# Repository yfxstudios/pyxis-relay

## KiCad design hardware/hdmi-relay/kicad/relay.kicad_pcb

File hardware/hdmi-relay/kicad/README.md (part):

# Carrier board rev A: KiCad project

**Current state (Oct 25):** schematic and board complete, ERC 0, DRC with schematic parity 0/0/0, fab outputs in
`fab/` (J301 hand-fitted, kept out of the JLCPCB BOM and CPL). The latest review is `REVIEW_FINAL_5.md`; the
sections below are the design history in date order, so the early ones describe drafts that no longer apply.

Open `relay.kicad_pro` in KiCad 10. **[relay.pdf](relay.pdf)** is the schematic as a PDF, 8 pages.

The schematic is **generated** from the Python files in `gen/`, one per sheet, so every connection is written down
next to the reason for it.

```bash
gen/check.sh        # regenerate, run KiCad's electrical rules check (ERC), print problems and every net
```

After editing a `gen/*.py` file, run it again; the `.kicad_sch` files are overwritten. If you'd rather edit in
KiCad's editor from here on, that's fine too: stop using the generator, since a regenerate would undo those edits.

## Sheets

| Sheet | File | What's on it |
|---|---|---|
| Power | `gen/power.py` | DC jack (PJ-002AH), NP-F contacts, USB-C with CH224A (PD 9 V), Schottky OR, fuse, TVS, battery sense, two SY8303 (5V_SOM for the module, 5V_SYS), two TPS563201 (3V3_IO, 1V1_628) |
| HDMI in (RK628D) | `gen/hdmi_in.py` | HDMI connector, ESD, plug detect, DDC, CEC and HPD; RK628D with its power switch, filtering and decoupling; 24 MHz crystal; CSI-2 x4 out. Copied from the DshanPi-A1 V1.1 schematic, pages 31–32. |
| HDMI out | `gen/board_io_sheets.py` | HDMI connector from the module's HDMI TX, ESD, 5 V current-limited switch (DDC/HPD level-shifted on the module) |
| Ethernet | `gen/ethernet.py` | Gigabit jack with magnetics and centre-tap capacitors; the PHY is on the Radxa CM3 |
| M.2 Wi-Fi + Bluetooth | `gen/board_io_sheets.py` | M.2 2230 E-key socket for the RTL8822CE: PCIe x1 for Wi-Fi, USB 2.0 for Bluetooth |
| Debug, buttons, LEDs, SDI | `gen/board_io_sheets.py` | Debug UART header, RESET and RECOVERY buttons, three LEDs, 2 × 20 SDI add-on header (not fitted), mounting holes |
| Module: Radxa CM3 | `gen/module.py`, `gen/cm3_pinout.json` | The three DF40 receptacles with Radxa's pin names (module revision V1.32+), every pin assigned or no-connect; recovery pull-up, VBUSDET, decoupling |

**Status (schematic draft 1, Oct 21; superseded, see the top):**
- ERC passed with one warning: the M.2 socket footprint wasn't made yet.
- 191 parts.
- Every RK628D ball (144) is assigned and checked against the datasheet ball map.
- Every Radxa CM3 pin (300) is assigned or marked unused; the build fails if one is missed or used twice.

## Before this could become a board (Oct 21 list, all done since)

1. **Check the module connectors:**
   - Compare our three DF40 receptacles with Radxa's IO-board connector data
     (`../datasheets/radxa_cm3_io_board_b2b_connector_20230718.asc`): pin 1 orientation, the spacing between
     connectors, and the M2.5 mounting holes.
   - J68's pads are Radxa pins 101–200 minus 100; check that against the IO board too.
2. **Footprints still to make or confirm:**
   - **M.2 E-key socket:** for the chosen part.
   - **Gigabit magjack:** pick an LCSC part with the Pulse JK0654219 pinout, or redo that footprint.
   - **HDMI connector:** the bought LCSC part (C2902698) vs. the Molex footprint used now.
   - **RK628D:** check the generated 0.65 mm BGA footprint (`relay.pretty/`) against the datasheet land pattern
     and JLCPCB's BGA rules.
   - **Locking DC jack:** pick it together with the case.
3. **Values to confirm:**
   - **Crystal load capacitors (18 pF):** match the chosen 24 MHz crystal's rated load capacitance.
   - **Inductor saturation currents.**
   - **The RK628D 1.1 V current:** for the Rockchip RK628D hardware design guide, which we don't have yet.
4. **Layout:** 4-layer impedance-controlled stack, rules in `../REV_A_SPEC.md` section 6, length limits from the
   Radxa CM3 datasheet.

## Board: first placement (Oct 22)

`relay.kicad_pcb` is generated by `gen/pcb.py` from the schematic netlist. Run it with KiCad's bundled Python:

```bash
/Applications/KiCad/KiCad.app/Contents/Frameworks/Python.framework/Versions/Current/bin/python3 gen/pcb.py
```

Renders: [3D view](renders/rev_a_placement_3d.png), [top view](renders/rev_a_placement_top.png).

**What it sets up:**
- **Board:** 120 × 100 mm, 4 layers.
- **Front panel:** HDMI IN and HDMI OUT.
- **Back panel:** USB-C, DC, the NP-F lead and RJ45.
- **Net classes:** in `relay.kicad_pro`.

  | Class | Width / gap |
  |---|---|
  | 100 Ω differential (HDMI, CSI, Ethernet) | 0.10 / 0.10 mm |
  | 90 Ω differential (USB) | 0.12 / 0.10 mm |
  | 85 Ω differential (PCIe) | 0.14 / 0.10 mm |
  | Power | 0.5 mm |
  | Default | 0.127 mm |

  These are first estimates for JLCPCB's JLC04161H-3313 stackup. **Confirm each with JLCPCB's impedance
  calculator.**
- **Module connectors and mounting holes:** copied from Radxa's own CM3 IO board (`relay.pretty/Radxa_CM3_*`,
  from `../datasheets/radxa_cm3_io_board_b2b_connector_20230718.asc`). The three receptacles and the four M2.5
  holes share one origin, so their spacing matches Radxa's working board exactly. Radxa's pad rows are 2.66 mm
  apart, against 3.08 mm in KiCad's stock DF40 footprint, so ours copy Radxa's.

**Placement:**
- **The CM3** sits in the middle, turned so J68 (camera input, HDMI out, PCIe) faces the front.
- **The RK628D** is between HDMI IN and the CM3's camera pins, so that run is short.
- **The M.2 Wi-Fi socket** is on the left, with the card lying over the board.
- **Power** is along the back-left; the SDI header (not fitted) is on the right.
- **Small parts** are packed by sheet into regions near their main chip (`REGIONS` in `gen/pcb.py`).

**DRC:** no clearance, short or overlap errors. What remains:
- **499 unrouted connections:** routing is next.
- **Labels overlapping:** cosmetic.
- **Edge connectors at the board edge:** expected; they sit at or slightly past it.

**Next, in order:**
1. **Hand placement:**
   - Every decoupling capacitor at its pin: the RK628D's 1.1 V and 3.3 V balls, the module's 5 V pins.
   - Each converter as a tight loop: input capacitor, switch node, inductor, output capacitor.
   - Crystals next to their chips.
   - ESD arrays at the connectors.
2. **Route the critical signals first:**
   - CSI from the RK628D to J68.
   - HDMI IN to the RK628D, and J68 to HDMI OUT.
   - PCIe to the M.2 socket; USB.
   - The Ethernet pairs from J69 to the RJ45.
   - Then power, a solid ground on L2, power on L3.
3. **Before ordering:**
   - Replace the M.2 placeholder footprint with the chosen socket's land pattern.
   - Confirm the HDMI, RJ45 (gigabit, JK0654219 pinout) and DC-jack footprints against the bought parts.
   - Fit the board size to the case.

## Routing: first traces (Oct 22)

`gen/route.py` adds the planes and the high-speed routes. It clears all tracks, vias and zones first, so run
`gen/pcb.py` and then `gen/route.py` after any placement change. Picture: [routes](renders/rev_a_first_routes.png),
traces only, without the copper pours.

**Placement changes for routing:**
- **RK628D turned 180°:** its CSI balls face J68 and its HDMI RX balls face HDMI IN.
- **HDMI IN ESD parts:** now in line under the connector. The schematic now gives each part two neighbouring pairs
  (D201: D2 and D1; D202: D0 and CLK), so all four pairs pass straight through.
- **Small parts:** moved out of the two routing channels.

**Planes:**
- **L2 and L3:** solid GND. L3 gets power islands when power is routed.
- **L1 and L4:** GND pours.

**Routed: 9 pairs, all 100 Ω, 0.10/0.10 mm.**
- **CSI-2, 5 lanes:** RK628D to J68.
  - D0, D1 and CLK run on L1 around the connector's west end and come up into the south pad row.
  - D2 and D3 hop under them on L4 (four vias each, a GND return via beside each). They come up between J68's pad
    rows into the north row.
- **HDMI IN, 4 pairs:** J201 to the RK628D, all on L1.
- **Within each pair:** P and N match to 0.01 mm, using small bumps on the shorter trace.
- **Between lanes:** lengths differ (CSI 26.2–33.5 mm, HDMI 23.8–30.2 mm). These aren't matched yet; compare
  against Rockchip's layout guide once we have it.

**DRC:**
- **No clearance, short or crossing errors.**
- **What remains:** 373 unrouted connections, silkscreen overlaps, and the USB-C pads at the board edge.

## Routing: RK628D decoupling and power (Oct 22)

Also done by `gen/route.py`, now with [gen/router.py](gen/router.py): a small grid maze router (A* on a 0.05 or
0.025 mm grid, 45° segments only, bend and via costs), since no autorouter is installed. A full run takes about
5 minutes. Pictures: [front](renders/rev_a_rk628d_front.png), [back](renders/rev_a_rk628d_back.png).

**Under the chip:**
- **Every power and GND ball** gets a dogbone to its own via: 49 vias, 0.3 mm with a 0.15 mm drill, centred
  between four balls.
- **Neighbouring balls on the same rail** are also tied on the top layer.
- **Nine inner signal balls** have a via site reserved for when the low-speed signals are routed.
- **Placement check:** the fanout makes sure no rail's via gets boxed in by other nets. Under the chip a trace can
  only move diagonally between vias: JLCPCB needs 0.2 mm from a via hole to any track, which leaves no room
  between two vias in a row.

**Rails:**
- **Order:** each rail is routed first, while the back and L3 are empty. Its vias join with 0.1 mm traces on L3
  (In2) and the back, out to an exit via just outside the ball field.
- **Net classes:** RK628D_3V3, the two AVDD rails and 1V1_628 moved from the POWER class to Default (0.1 mm
  clearance) so these traces fit between the vias.

**Decoupling:**
- **All 29 capacitors and both ferrites** for these rails are now on the back, under and around the chip.
- **Placement:** each 100 nF capacitor is placed at the spot nearest its ball. A spot is kept only after a trial
  route reaches both pads; if the route fails, the next spot is tried.
- **Ground:** capacitor ground pads go to a GND fanout via, or to a GND via of their own.

**1.1 V converter (U106 TPS563201):**
- **Moved next to the RK628D,** its only load, from the power section.
- **Routing:** its switch node, input and output are routed locally, with a GND via at every ground pad.
- **Feeds:** 1V1_628 runs to the ferrite and the core balls. RK628D_3V3 runs from the P-FET (Q201) to the
  pull-ups, the ferrite and the converter's enable.

**DRC:**
- **No clearance, short, hole or dangling errors.**
- **Every RK628D rail and every 1.1 V converter net is fully connected.**
- **300 connections are left** for the rest of the board. Four of them are ground-pour islands, which the
  stitching grid will join.

**Still open here:**
- **Converter input:** 5V_SYS into the converter, and 3V3_IO into Q201, come from the main converters, so they're
  routed with the power section.
- **Small vias cost extra:** JLCPCB charges more for vias under 0.45 mm. The 0.65 mm ball grid needs them.
- **Trace current:** the 0.1 mm rail traces under the chip are fine for the RK628D's currents as far as we know.
  Check against the RK628D's actual figures once we have Rockchip's guide.
- **Trial-routing message:** the run prints that FB201's trial route failed. The final pass connects it anyway;
  DRC shows it connected.

## Routing: RK628D low-speed signals (Oct 22)

Picture: [signals](renders/rev_a_rk628d_signals.png) (top red, back blue, no pours).

**Workflow:**
- `gen/route.py`: placement and routing, about 10 minutes. It saves `routed.kicad_pcb` (no pours).
- `gen/finish.py`: about 1 second. It removes duplicate vias, adds the GND pours, fills them and writes
  `relay.kicad_pcb`.
- **For a small change,** script it against `routed.kicad_pcb` and run `gen/finish.py` alone. It copies
  `relay.kicad_pro` next to the checkpoint first: KiCad rewrites the project file (net classes and rules) from
  the board it loaded.

**Support parts re-placed by function:**
- `gen/pcb.py` had packed them by size, which put the crystal's load capacitors 20 mm from the crystal.
- `gen/route.py` now places each of 39 parts next to what it connects to: a ball first, then the part before it.
- **Examples:**
  - The crystal and its load capacitors sit right above the XIN/XOUT balls.
  - The DDC/CEC/HPD resistors sit between the chip and the HDMI port; the port ESD is at the connector.
  - The RK628D power switch (Q201/Q202) is to the west.
- **Keep-outs:** nothing goes under the CM3, and a 1.5 mm ring around the RK628D stays free for its escape traces.

**Routing:**
- **31 signal nets,** plus HDMIRX_5V and the local 3V3_IO.
- **Chip end:** each net's chip end is routed on the 0.025 mm grid, where the gaps between balls fall on cells.
  The rest uses the 0.05 mm grid, and the runs down to the CM3's J69 use a board-wide grid.
- **Inner balls:** the nine inner signal balls get their reserved via (placed with the power fanout). Signals
  route before the capacitors take the back.
- **Retries:** if any net fails, all local routes are taken out and retried with the failed nets first; the best
  of 4 passes is kept.
- **Clean-up:** dead ends are removed using KiCad's own connectivity check.

**Result:**
- **DRC:** no clearance, short, hole or dangling errors. 254 connections are left on the whole board (was 300).
- **13 RK628D connections are still open:**
  - **Chip to its parts:** XOUT, RX_SDA, RX_CEC, EFUSE, I2S_MCLK, and I2C SCL/SDA to their pull-ups.
  - **To J69:** I2C_SCL, CEC_GPIO and RK628D_PWR_EN.
  - **Rails:** FB202's 1V1_628 side, and one AVDD_3V3 and one AVDD_1V1 capacitor.
- **Why the router stalls:** they stay open whatever the order. The area north of the chip is congested, and this
  router has no true rip-up, so the remaining 13 should be finished by hand in KiCad's interactive router (a few
  minutes each), or with Freerouting (needs Java).

**Freerouting tried (Oct 22), not kept:**
- **Setup:** Freerouting 2.5.0 is at `~/tools/freerouting/` (checksum checked against the GitHub release), with
  Homebrew's OpenJDK 27.
- **[gen/freeroute.py](gen/freeroute.py):**
  - **Export:** locks every existing track and exports the board.
  - **Other nets:** hides them by splitting each into single-pin nets. Moving them to "no net" made Freerouting
    ignore them as obstacles, and routing all ~250 open connections took over 20 minutes.
  - **Import:** brings back only new outer-layer copper on the target nets. KiCad's own session import replaces
    every track.
- **Result:** Freerouting connected only the two capacitors. It left the other 11 open and added DRC errors
  (unconnected vias, hole clearance), so the board was put back to the checkpoint.

## Routing: HDMI OUT (Oct 22)

[gen/hdmi_out.py](gen/hdmi_out.py) runs on `routed.kicad_pcb` in about 2 minutes. `gen/route.py` also calls it for
a full rebuild (not yet re-run that way). Picture: [HDMI OUT](renders/rev_a_hdmi_out.png).

**Schematic:**
- **ESD order:** the parts now take their lines in connector-pin order, as on HDMI IN.
  - D401: D2 and D1.
  - D402: D0 and CLK.
  - D403: SCL, SDA, 5 V and HPD.

**TMDS pairs:**
- **Path:** the four pairs leave J68's north pad row (1.2 mm apart, P west), step east on one 45° leg to the
  connector's 1.5 mm spacing, and pass straight through the ESD parts behind J401. All on L1.
- **Lengths:** 22.65, 22.77, 22.89 and 23.02 mm (D2, D1, D0, CLK). Within each pair, P and N match exactly.

**Low-speed:**
- **DDC and 5 V:** routed east of the pairs. The 5 V line runs straight through D403 at 0.25 mm.
- **Hot-plug:** crosses the pairs on the back to J68 pin 153.
- **Parts:** the 5 V switch (U401), its capacitors and the DDC pull-ups sit east of the pair corridor.

**DRC:**
- **No electrical errors.**
- **HDMI OUT connected, except** the 5V_SYS feed into U401, which comes with the power section.

## Routing: Ethernet (Oct 23)

[gen/rest.py](gen/rest.py)'s `ethernet` section runs on the checkpoint in about 40 seconds.

**Route:**
- **Where they go:** the four pairs (L1, over the L2 plane) leave J69's west end. MDI0/MDI1 go north; MDI2/MDI3 go
  through the gap between its pad rows and round its end.
- **Lanes:** they run east in four lanes between J1's bottom pins and the CM3's mounting hole, then come down into
  the magjack through the gap in its LED row.
- **Polarity:** each pair turns into its own pins from its own strip, so P and N land on the right pins with no
  crossing.
- **Lengths:** 53–70 mm; P and N within 0.7 mm of each other in every pair.
- **Centre taps:** the four centre-tap capacitors are on the back, beside their jack pins, each with a GND via.

**RK628D lines to J69:** the lines down to J69 (interrupt, plug detect, reset, I2C, CEC, power enable) were
re-routed around the lanes; they cross them on the back.

**DRC:** no electrical errors. 199 connections are left.

**M.2 socket (in progress):**
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
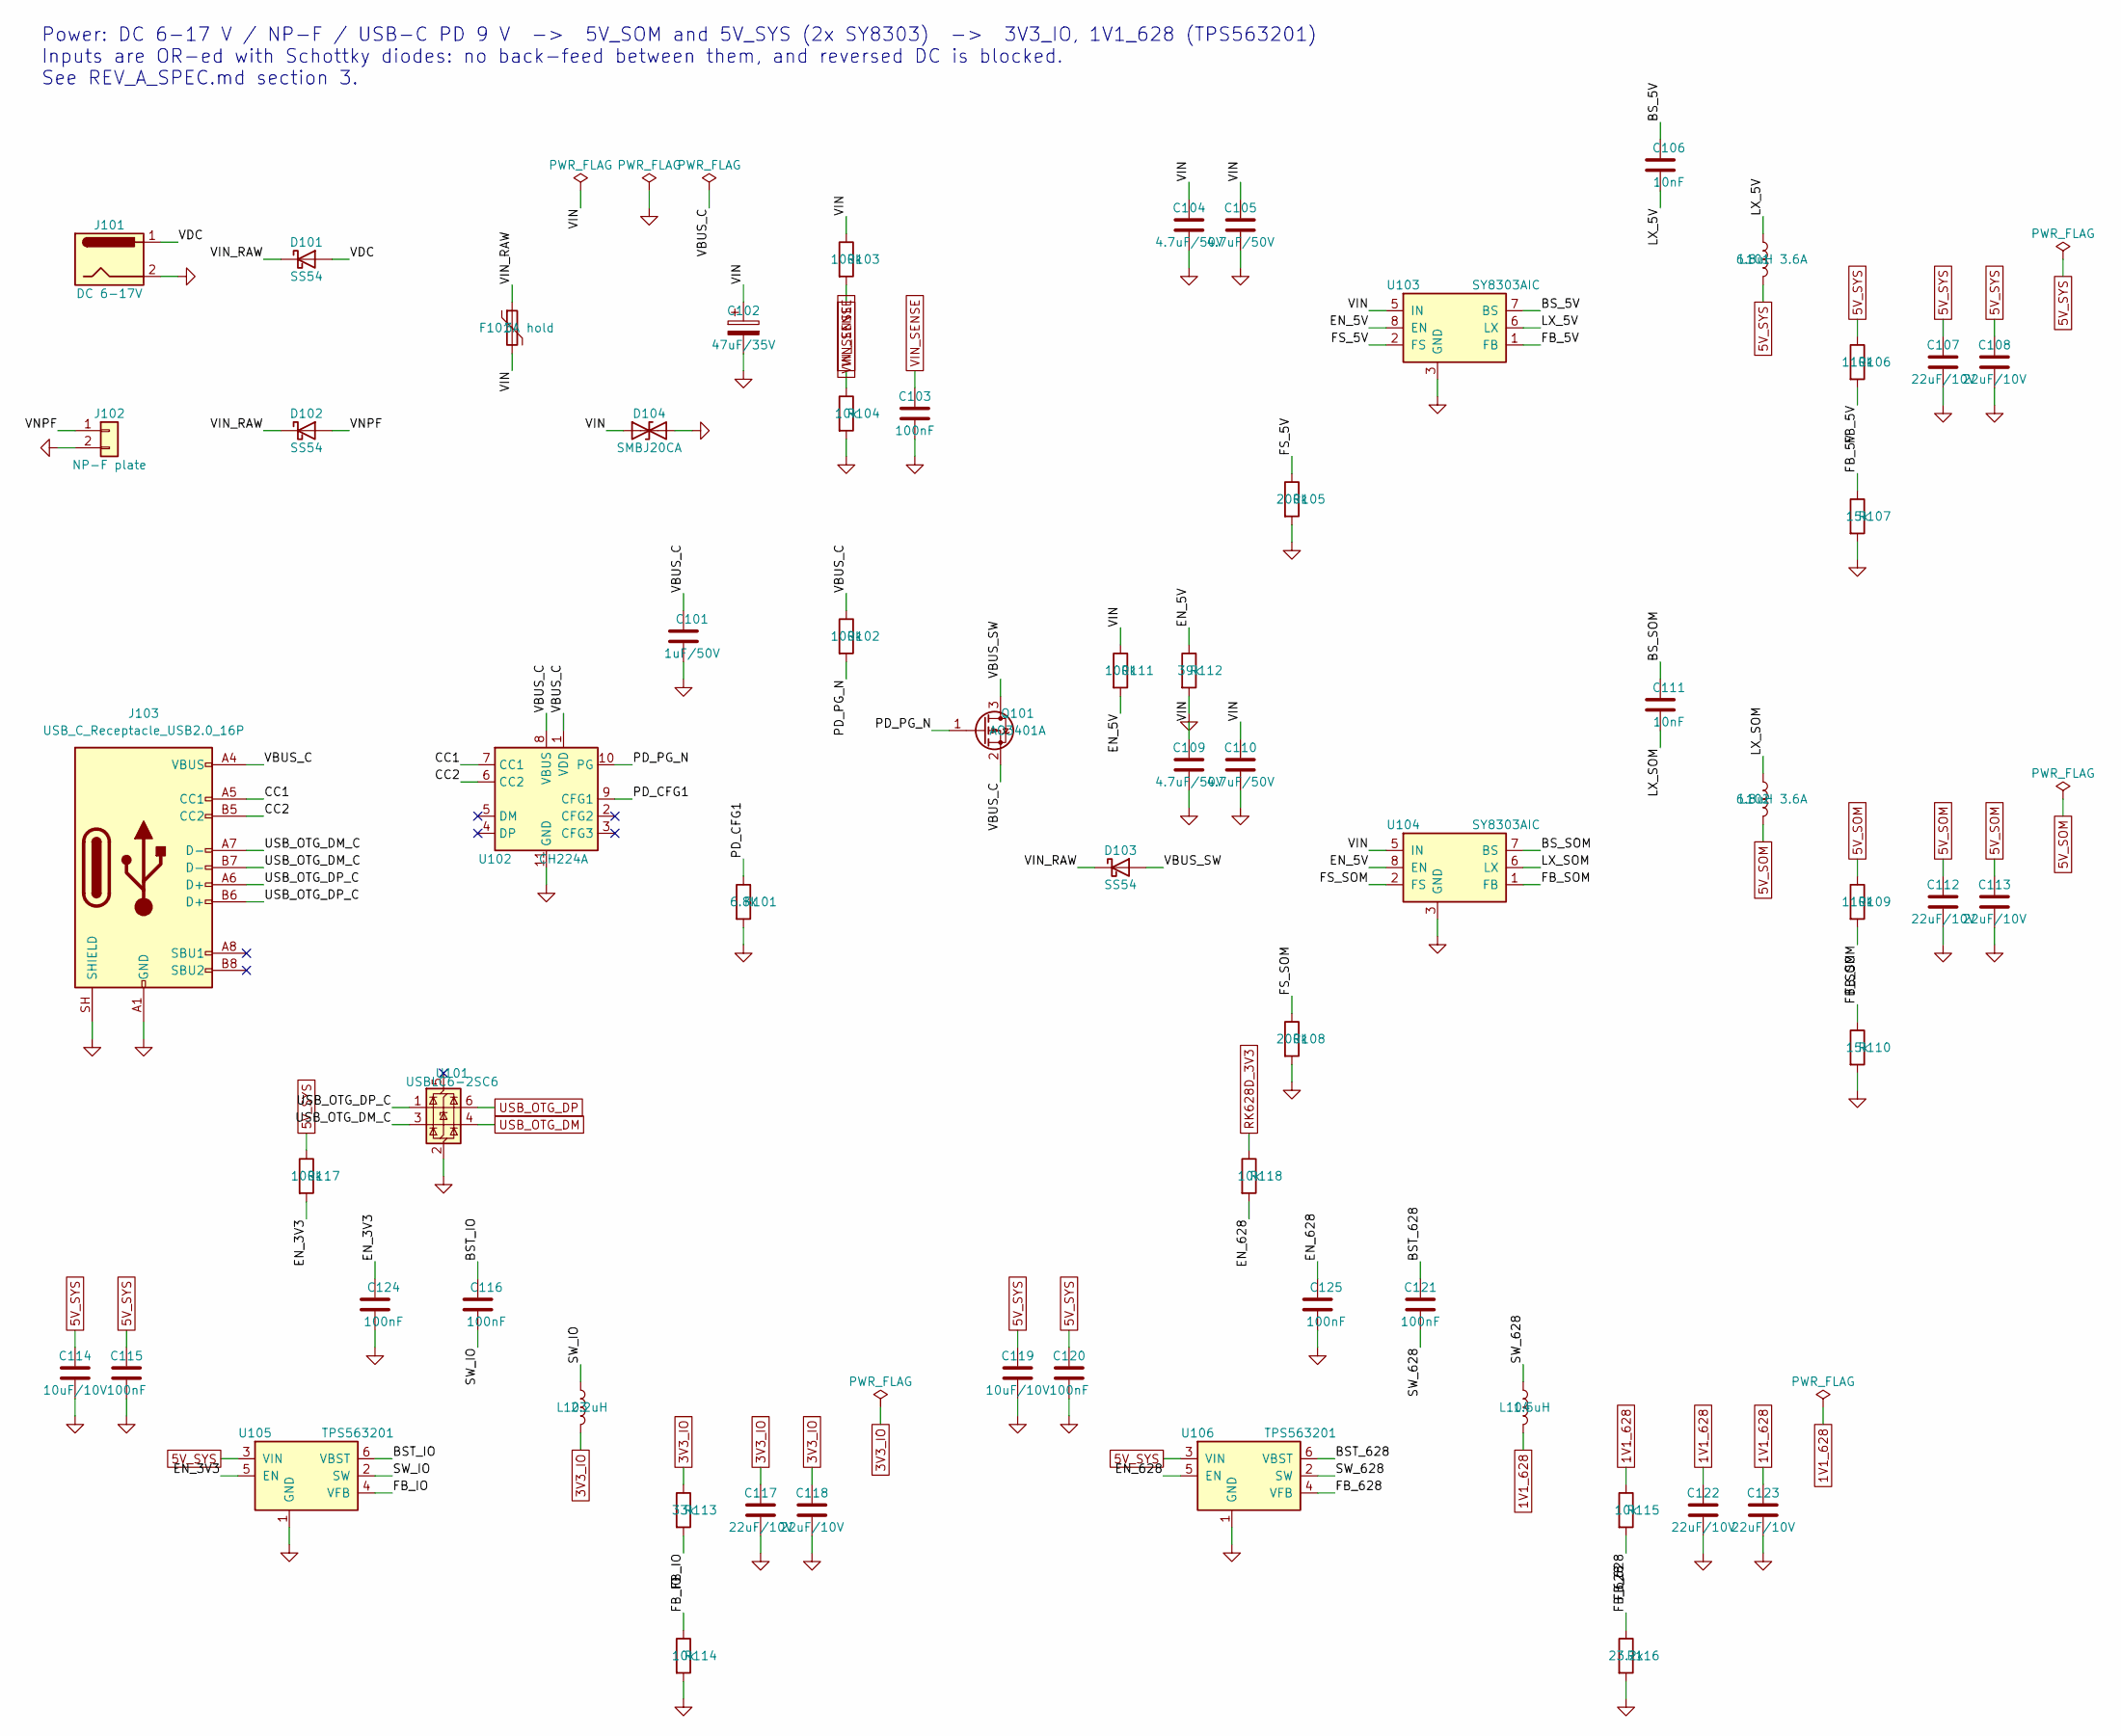
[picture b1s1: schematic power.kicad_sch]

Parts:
C101: 1uF/50V; C_0805_2012Metric
C102: 47uF/35V; CP_Elec_6.3x7.7
C103, C115, C116, C120, C121, C124, C125: 100nF; C_0402_1005Metric
C104, C105, C109, C110: 4.7uF/50V; C_1206_3216Metric
C106, C111: 10nF; C_0402_1005Metric
C107, C108, C112, C113, C117, C118, C122, C123: 22uF/10V; C_0805_2012Metric
C114, C119: 10uF/10V; C_0805_2012Metric
D101, D102, D103: SS54; D_SMA
D104: SMBJ20CA; D_SMB
F101: 3A hold; Fuse_1812_4532Metric
J101: DC 6-17V; BarrelJack_Horizontal
J102: NP-F plate; JST_PH_B2B-PH-K_1x02_P2.00mm_Vertical
J103: USB_C_Receptacle_USB2.0_16P; USB_C_Receptacle_HRO_TYPE-C-31-M-12; LCSC C165948
L101, L102: 6.8uH 3.6A; L_Bourns_SRN6045TA
L103: 2.2uH; L_Bourns_SRN6045TA
L104: 1.5uH; L_Bourns_SRN6045TA
Q101: AO3401A; SOT-23; LCSC C15127
R101: 6.8k; R_0402_1005Metric
R102, R103, R111, R117: 100k; R_0402_1005Metric
R104, R114, R115, R118: 10k; R_0402_1005Metric
R105, R108: 200k; R_0402_1005Metric
R106, R109: 110k; R_0402_1005Metric
R107, R110: 15k; R_0402_1005Metric
R112: 39k; R_0402_1005Metric
R113: 33k; R_0402_1005Metric
R116: 23.2k; R_0402_1005Metric
U101: USBLC6-2SC6; SOT-23-6
U102: CH224A; SSOP-10-1EP_3.9x4.9mm_P1mm_EP2.1x3.3mm
U103, U104: SY8303AIC; TSOT-23-8; LCSC C97054
U105, U106: TPS563201; SOT-23-6; LCSC C116592

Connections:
1V1_628: C122.1, C123.1, L104.2, R115.1; also elsewhere on the board
3V3_IO: C117.1, C118.1, L103.2, R113.1; also elsewhere on the board
5V_SOM: C112.1, C113.1, L102.2, R109.1; also elsewhere on the board
5V_SYS: C107.1, C108.1, C114.1, C115.1, C119.1, C120.1, L101.2, R106.1, R117.1, U105.3 (VIN), U106.3 (VIN); also elsewhere on the board
/Power/BST_628: C121.1, U106.6 (VBST)
/Power/BST_IO: C116.1, U105.6 (VBST)
/Power/BS_5V: C106.1, U103.7 (BS)
/Power/BS_SOM: C111.1, U104.7 (BS)
/Power/CC1: J103.A5 (CC1), U102.7 (CC1)
/Power/CC2: J103.B5 (CC2), U102.6 (CC2)
/Power/EN_3V3: C124.1, R117.2, U105.5 (EN)
/Power/EN_5V: R111.2, R112.1, U103.8 (EN), U104.8 (EN)
/Power/EN_628: C125.1, R118.2, U106.5 (EN)
/Power/FB_5V: R106.2, R107.1, U103.1 (FB)
/Power/FB_628: R115.2, R116.1, U106.4 (VFB)
/Power/FB_IO: R113.2, R114.1, U105.4 (VFB)
/Power/FB_SOM: R109.2, R110.1, U104.1 (FB)
/Power/FS_5V: R105.1, U103.2 (FS)
/Power/FS_SOM: R108.1, U104.2 (FS)
/Power/LX_5V: C106.2, L101.1, U103.6 (LX)
/Power/LX_SOM: C111.2, L102.1, U104.6 (LX)
/Power/PD_CFG1: R101.1, U102.9 (CFG1)
/Power/PD_PG_N: Q101.1 (G), R102.2, U102.10 (PG)
/Power/SW_628: C121.2, L104.1, U106.2 (SW)
/Power/SW_IO: C116.2, L103.1, U105.2 (SW)
/Power/USB_OTG_DM_C: J103.A7 (D-), J103.B7 (D-), U101.3 (I/O2)
/Power/USB_OTG_DP_C: J103.A6 (D+), J103.B6 (D+), U101.1 (I/O1)
/Power/VBUS_C: C101.1, J103.A4 (VBUS), J103.A9 (VBUS), J103.B4 (VBUS), J103.B9 (VBUS), Q101.2 (S), R102.1, U102.1 (VDD), U102.8 (VBUS)
/Power/VBUS_SW: D103.2 (A), Q101.3 (D)
/Power/VDC: D101.2 (A), J101.1
/Power/VIN: C102.1, C104.1, C105.1, C109.1, C110.1, D104.1 (A1), F101.2, R103.1, R111.1, U103.5 (IN), U104.5 (IN)
/Power/VIN_RAW: D101.1 (K), D102.1 (K), D103.1 (K), F101.1
/Power/VNPF: D102.2 (A), J102.1
GND: C101.2, C102.2, C103.2, C104.2, C105.2, C107.2, C108.2, C109.2, C110.2, C112.2, C113.2, C114.2, C115.2, C117.2, C118.2, C119.2, C120.2, C122.2, C123.2, C124.2, C125.2, D104.2 (A2), J101.2, J102.2, J103.A1 (GND), J103.A12 (GND), J103.B1 (GND), J103.B12 (GND), J103.SH (SHIELD), R101.2, R104.2, R105.2, R107.2, R108.2, R110.2, R112.2, R114.2, R116.2, U101.2 (GND), U102.11 (GND), U103.3 (GND), U103.4 (GND), U104.3 (GND), U104.4 (GND), U105.1 (GND), U106.1 (GND); also elsewhere on the board
RK628D_3V3: R118.1; also elsewhere on the board
USB_OTG_DM: U101.4 (I/O2); also elsewhere on the board
USB_OTG_DP: U101.6 (I/O1); also elsewhere on the board
VIN_SENSE: C103.1, R103.2, R104.1; also elsewhere on the board

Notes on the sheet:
Power: DC 6-17 V / NP-F / USB-C PD 9 V -> 5V_SOM and 5V_SYS (2x SY8303) -> 3V3_IO, 1V1_628 (TPS563201) Inputs are OR-ed with Schottky diodes: no back-feed between them, and reversed DC is blocked. See REV_A_SPEC.md section 3.

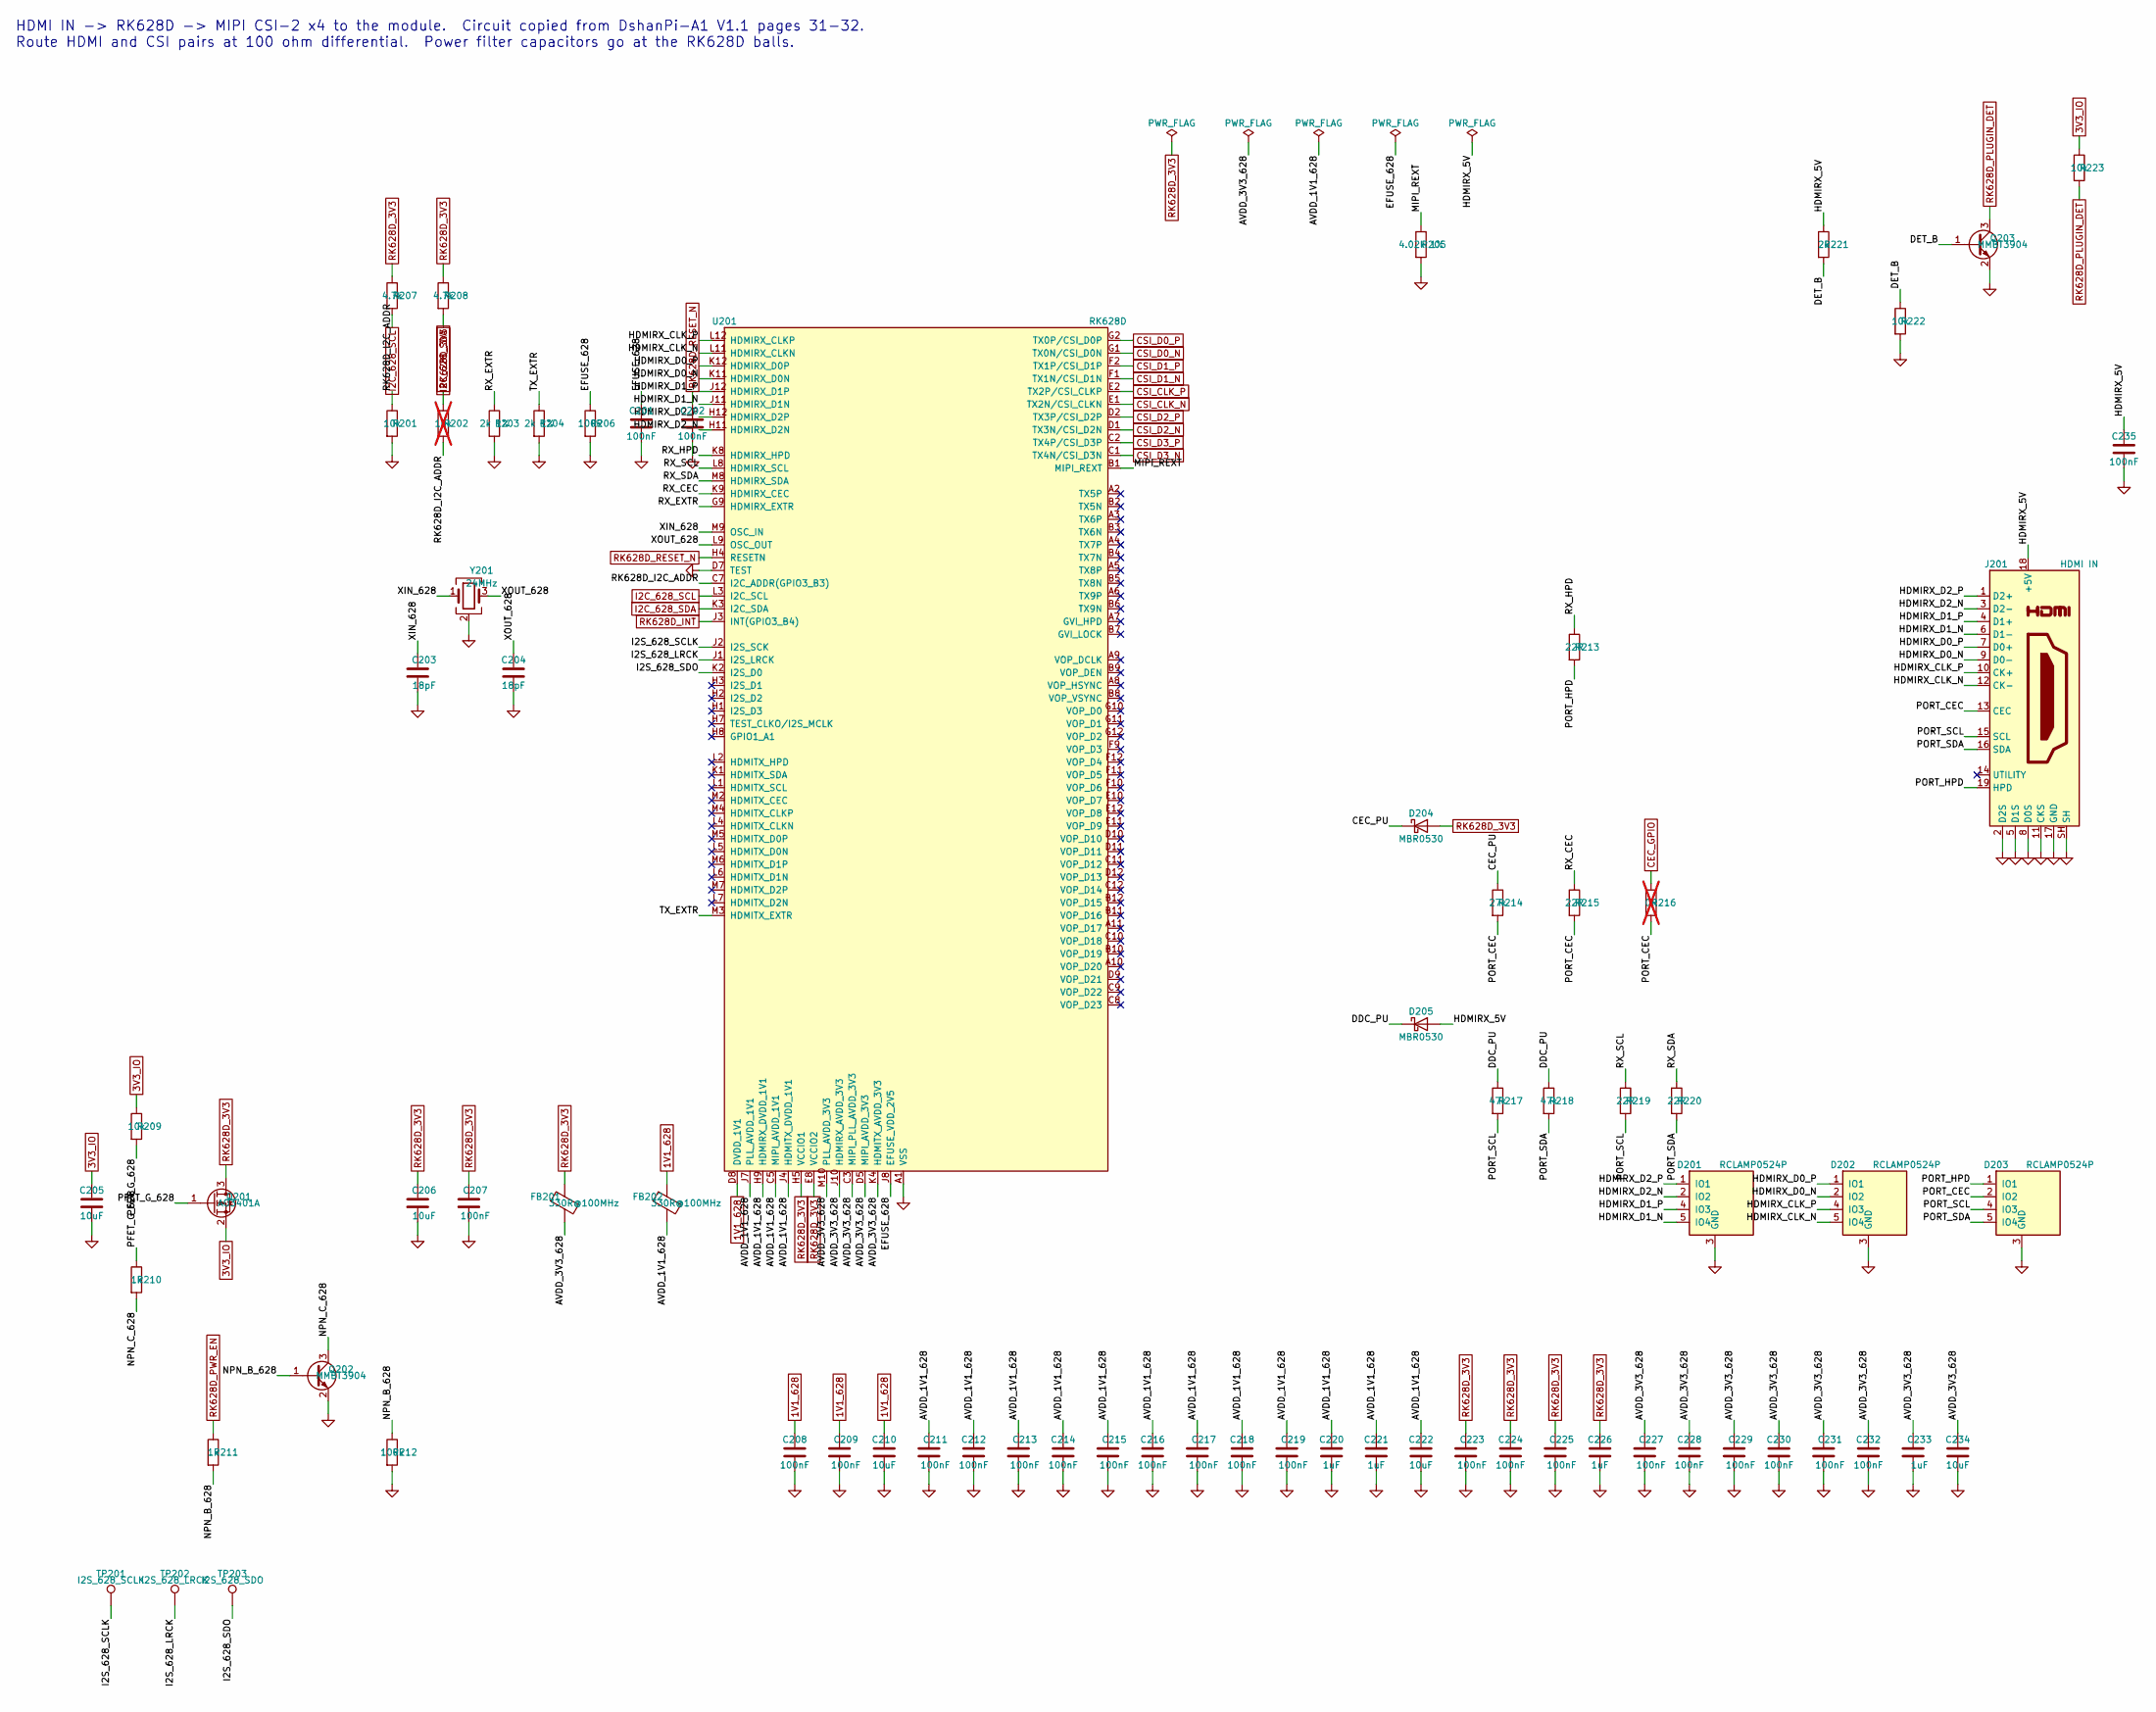
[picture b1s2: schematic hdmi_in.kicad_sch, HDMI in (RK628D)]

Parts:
C201, C202, C207, C208, C209, C211, C212, C213, C214, C215, C216, C217, C218, C219, C223, C224, C225, C227, C228, C229, C230, C231, C232, C235: 100nF; C_0402_1005Metric
C203, C204: 18pF; C_0402_1005Metric
C205, C206, C210, C222, C234: 10uF; C_0805_2012Metric
C220, C221, C226, C233: 1uF; C_0402_1005Metric
D201, D202, D203: RCLAMP0524P; USON-10_2.5x1.0mm_P0.5mm; LCSC C907837
D204, D205: MBR0530; D_SOD-123
FB201, FB202: 330R@100MHz; L_0603_1608Metric
J201: HDMI IN; HDMI_A_Molex_208658-1001_Horizontal
Q201: AO3401A; SOT-23; LCSC C15127
Q202, Q203: MMBT3904; SOT-23
R201, R209, R222, R223: 10k; R_0402_1005Metric
R202: 10k; R_0402_1005Metric; not fitted
R203, R204: 2k 1%; R_0402_1005Metric
R205: 4.02k 1%; R_0402_1005Metric
R206: 100R; R_0402_1005Metric
R207, R208: 4.7k; R_0402_1005Metric
R210, R211: 1k; R_0402_1005Metric
R212: 100k; R_0402_1005Metric
R213, R215, R219, R220: 22R; R_0402_1005Metric
R214: 27k; R_0402_1005Metric
R216: 0R; R_0402_1005Metric; not fitted
R217, R218: 47k; R_0402_1005Metric
R221: 2k; R_0402_1005Metric
TP201: I2S_628_SCLK; TestPoint_Pad_D1.0mm
TP202: I2S_628_LRCK; TestPoint_Pad_D1.0mm
TP203: I2S_628_SDO; TestPoint_Pad_D1.0mm
U201: RK628D; BGA-144_8.0x8.0mm_Layout12x12_P0.65mm; LCSC C2843533
Y201: 24MHz; Crystal_SMD_3225-4Pin_3.2x2.5mm

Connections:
1V1_628: C208.1, C209.1, C210.1, FB202.1, U201.D8 (DVDD_1V1), U201.E9 (DVDD_1V1); also elsewhere on the board
3V3_IO: C205.1, Q201.2 (S), R209.1, R223.1; also elsewhere on the board
/HDMI in (RK628D)/AVDD_1V1_628: C211.1, C212.1, C213.1, C214.1, C215.1, C216.1, C217.1, C218.1, C219.1, C220.1, C221.1, C222.1, FB202.2, U201.C5 (MIPI_AVDD_1V1), U201.D4 (MIPI_AVDD_1V1), U201.E3 (MIPI_AVDD_1V1), U201.F3 (MIPI_AVDD_1V1), U201.H9 (HDMIRX_DVDD_1V1), U201.J4 (HDMITX_DVDD_1V1), U201.J5 (HDMITX_DVDD_1V1), U201.J6 (HDMITX_DVDD_1V1), U201.J7 (PLL_AVDD_1V1), U201.J9 (HDMIRX_DVDD_1V1)
/HDMI in (RK628D)/AVDD_3V3_628: C227.1, C228.1, C229.1, C230.1, C231.1, C232.1, C233.1, C234.1, FB201.2, U201.C3 (MIPI_PLL_AVDD_3V3), U201.D5 (MIPI_AVDD_3V3), U201.E4 (MIPI_AVDD_3V3), U201.J10 (HDMIRX_AVDD_3V3), U201.K4 (HDMITX_AVDD_3V3), U201.M10 (PLL_AVDD_3V3)
/HDMI in (RK628D)/CEC_PU: D204.1 (K), R214.1
/HDMI in (RK628D)/DDC_PU: D205.1 (K), R217.1, R218.1
/HDMI in (RK628D)/DET_B: Q203.1 (B), R221.2, R222.1
/HDMI in (RK628D)/EFUSE_628: C201.1, R206.1, U201.J8 (EFUSE_VDD_2V5)
/HDMI in (RK628D)/HDMIRX_5V: C235.1, D205.2 (A), J201.18 (+5V), R221.1
/HDMI in (RK628D)/HDMIRX_CLK_N: D202.5 (IO4), D202.6 (IO4), J201.12 (CK-), U201.L11 (HDMIRX_CLKN)
/HDMI in (RK628D)/HDMIRX_CLK_P: D202.4 (IO3), D202.7 (IO3), J201.10 (CK+), U201.L12 (HDMIRX_CLKP)
/HDMI in (RK628D)/HDMIRX_D0_N: D202.2 (IO2), D202.9 (IO2), J201.9 (D0-), U201.K11 (HDMIRX_D0N)
/HDMI in (RK628D)/HDMIRX_D0_P: D202.1 (IO1), D202.10 (IO1), J201.7 (D0+), U201.K12 (HDMIRX_D0P)
/HDMI in (RK628D)/HDMIRX_D1_N: D201.5 (IO4), D201.6 (IO4), J201.6 (D1-), U201.J11 (HDMIRX_D1N)
/HDMI in (RK628D)/HDMIRX_D1_P: D201.4 (IO3), D201.7 (IO3), J201.4 (D1+), U201.J12 (HDMIRX_D1P)
/HDMI in (RK628D)/HDMIRX_D2_N: D201.2 (IO2), D201.9 (IO2), J201.3 (D2-), U201.H11 (HDMIRX_D2N)
/HDMI in (RK628D)/HDMIRX_D2_P: D201.1 (IO1), D201.10 (IO1), J201.1 (D2+), U201.H12 (HDMIRX_D2P)
/HDMI in (RK628D)/I2S_628_LRCK: TP202.1, U201.J1 (I2S_LRCK)
/HDMI in (RK628D)/I2S_628_SCLK: TP201.1, U201.J2 (I2S_SCK)
/HDMI in (RK628D)/I2S_628_SDO: TP203.1, U201.K2 (I2S_D0)
/HDMI in (RK628D)/MIPI_REXT: R205.1, U201.B1 (MIPI_REXT)
/HDMI in (RK628D)/NPN_B_628: Q202.1 (B), R211.2, R212.1
/HDMI in (RK628D)/NPN_C_628: Q202.3 (C), R210.2
/HDMI in (RK628D)/PFET_G_628: Q201.1 (G), R209.2, R210.1
/HDMI in (RK628D)/PORT_CEC: D203.2 (IO2), D203.9 (IO2), J201.13 (CEC), R214.2, R215.2, R216.2
/HDMI in (RK628D)/PORT_HPD: D203.1 (IO1), D203.10 (IO1), J201.19 (HPD), R213.2
/HDMI in (RK628D)/PORT_SCL: D203.4 (IO3), D203.7 (IO3), J201.15 (SCL), R217.2, R219.2
/HDMI in (RK628D)/PORT_SDA: D203.5 (IO4), D203.6 (IO4), J201.16 (SDA), R218.2, R220.2
/HDMI in (RK628D)/RK628D_I2C_ADDR: R201.1, R202.2, U201.C7 (I2C_ADDR(GPIO3_B3))
/HDMI in (RK628D)/RX_CEC: R215.1, U201.K9 (HDMIRX_CEC)
/HDMI in (RK628D)/RX_EXTR: R203.1, U201.G9 (HDMIRX_EXTR)
/HDMI in (RK628D)/RX_HPD: R213.1, U201.K8 (HDMIRX_HPD)
/HDMI in (RK628D)/RX_SCL: R219.1, U201.L8 (HDMIRX_SCL)
/HDMI in (RK628D)/RX_SDA: R220.1, U201.M8 (HDMIRX_SDA)
/HDMI in (RK628D)/TX_EXTR: R204.1, U201.M3 (HDMITX_EXTR)
/HDMI in (RK628D)/XIN_628: C203.1, U201.M9 (OSC_IN), Y201.1
/HDMI in (RK628D)/XOUT_628: C204.1, U201.L9 (OSC_OUT), Y201.3
CEC_GPIO: R216.1; also elsewhere on the board
CSI_CLK_N: U201.E1 (TX2N/CSI_CLKN); also elsewhere on the board
CSI_CLK_P: U201.E2 (TX2P/CSI_CLKP); also elsewhere on the board
CSI_D0_N: U201.G1 (TX0N/CSI_D0N); also elsewhere on the board
CSI_D0_P: U201.G2 (TX0P/CSI_D0P); also elsewhere on the board
CSI_D1_N: U201.F1 (TX1N/CSI_D1N); also elsewhere on the board
CSI_D1_P: U201.F2 (TX1P/CSI_D1P); also elsewhere on the board
CSI_D2_N: U201.D1 (TX3N/CSI_D2N); also elsewhere on the board
CSI_D2_P: U201.D2 (TX3P/CSI_D2P); also elsewhere on the board
CSI_D3_N: U201.C1 (TX4N/CSI_D3N); also elsewhere on the board
CSI_D3_P: U201.C2 (TX4P/CSI_D3P); also elsewhere on the board
GND: C201.2, C202.2, C203.2, C204.2, C205.2, C206.2, C207.2, C208.2, C209.2, C210.2, C211.2, C212.2, C213.2, C214.2, C215.2, C216.2, C217.2, C218.2, C219.2, C220.2, C221.2, C222.2, C223.2, C224.2, C225.2, C226.2, C227.2, C228.2, C229.2, C230.2, C231.2, C232.2, C233.2, C234.2, C235.2, D201.3 (GND), D201.8 (GND), D202.3 (GND), D202.8 (GND), D203.3 (GND), D203.8 (GND), J201.2 (D2S), J201.5 (D1S), J201.8 (D0S), J201.11 (CKS), J201.17 (GND), J201.SH, Q202.2 (E), Q203.2 (E), R201.2, R203.2, R204.2, R205.2, R206.2, R212.2, R222.2, U201.A1 (VSS), U201.A12 (VSS), U201.C4 (VSS), U201.C6 (VSS), U201.D3 (VSS), U201.D6 (VSS), U201.D7 (TEST), U201.E5 (VSS), U201.E6 (VSS), U201.E7 (VSS), U201.F4 (VSS), U201.F5 (VSS), U201.F6 (VSS), U201.F7 (VSS), U201.G3 (VSS), U201.G4 (VSS), U201.G5 (VSS), U201.G6 (VSS), U201.G7 (VSS), U201.G8 (VSS), U201.H6 (VSS), U201.H10 (VSS), U201.K5 (VSS), U201.K6 (VSS), U201.K7 (VSS), U201.K10 (VSS), U201.L10 (VSS), U201.M1 (VSS), U201.M11 (VSS), U201.M12 (VSS), Y201.2 (G), Y201.4 (G); also elsewhere on the board
I2C_628_SCL: R207.2, U201.L3 (I2C_SCL); also elsewhere on the board
I2C_628_SDA: R208.2, U201.K3 (I2C_SDA); also elsewhere on the board
RK628D_3V3: C206.1, C207.1, C223.1, C224.1, C225.1, C226.1, D204.2 (A), FB201.1, Q201.3 (D), R202.1, R207.1, R208.1, U201.E8 (VCCIO2), U201.F8 (VCCIO2), U201.H5 (VCCIO1); also elsewhere on the board
RK628D_INT: U201.J3 (INT(GPIO3_B4)); also elsewhere on the board
RK628D_PLUGIN_DET: Q203.3 (C), R223.2; also elsewhere on the board
RK628D_PWR_EN: R211.1; also elsewhere on the board

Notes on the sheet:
HDMI IN -> RK628D -> MIPI CSI-2 x4 to the module. Circuit copied from DshanPi-A1 V1.1 pages 31-32. Route HDMI and CSI pairs at 100 ohm differential. Power filter capacitors go at the RK628D balls.

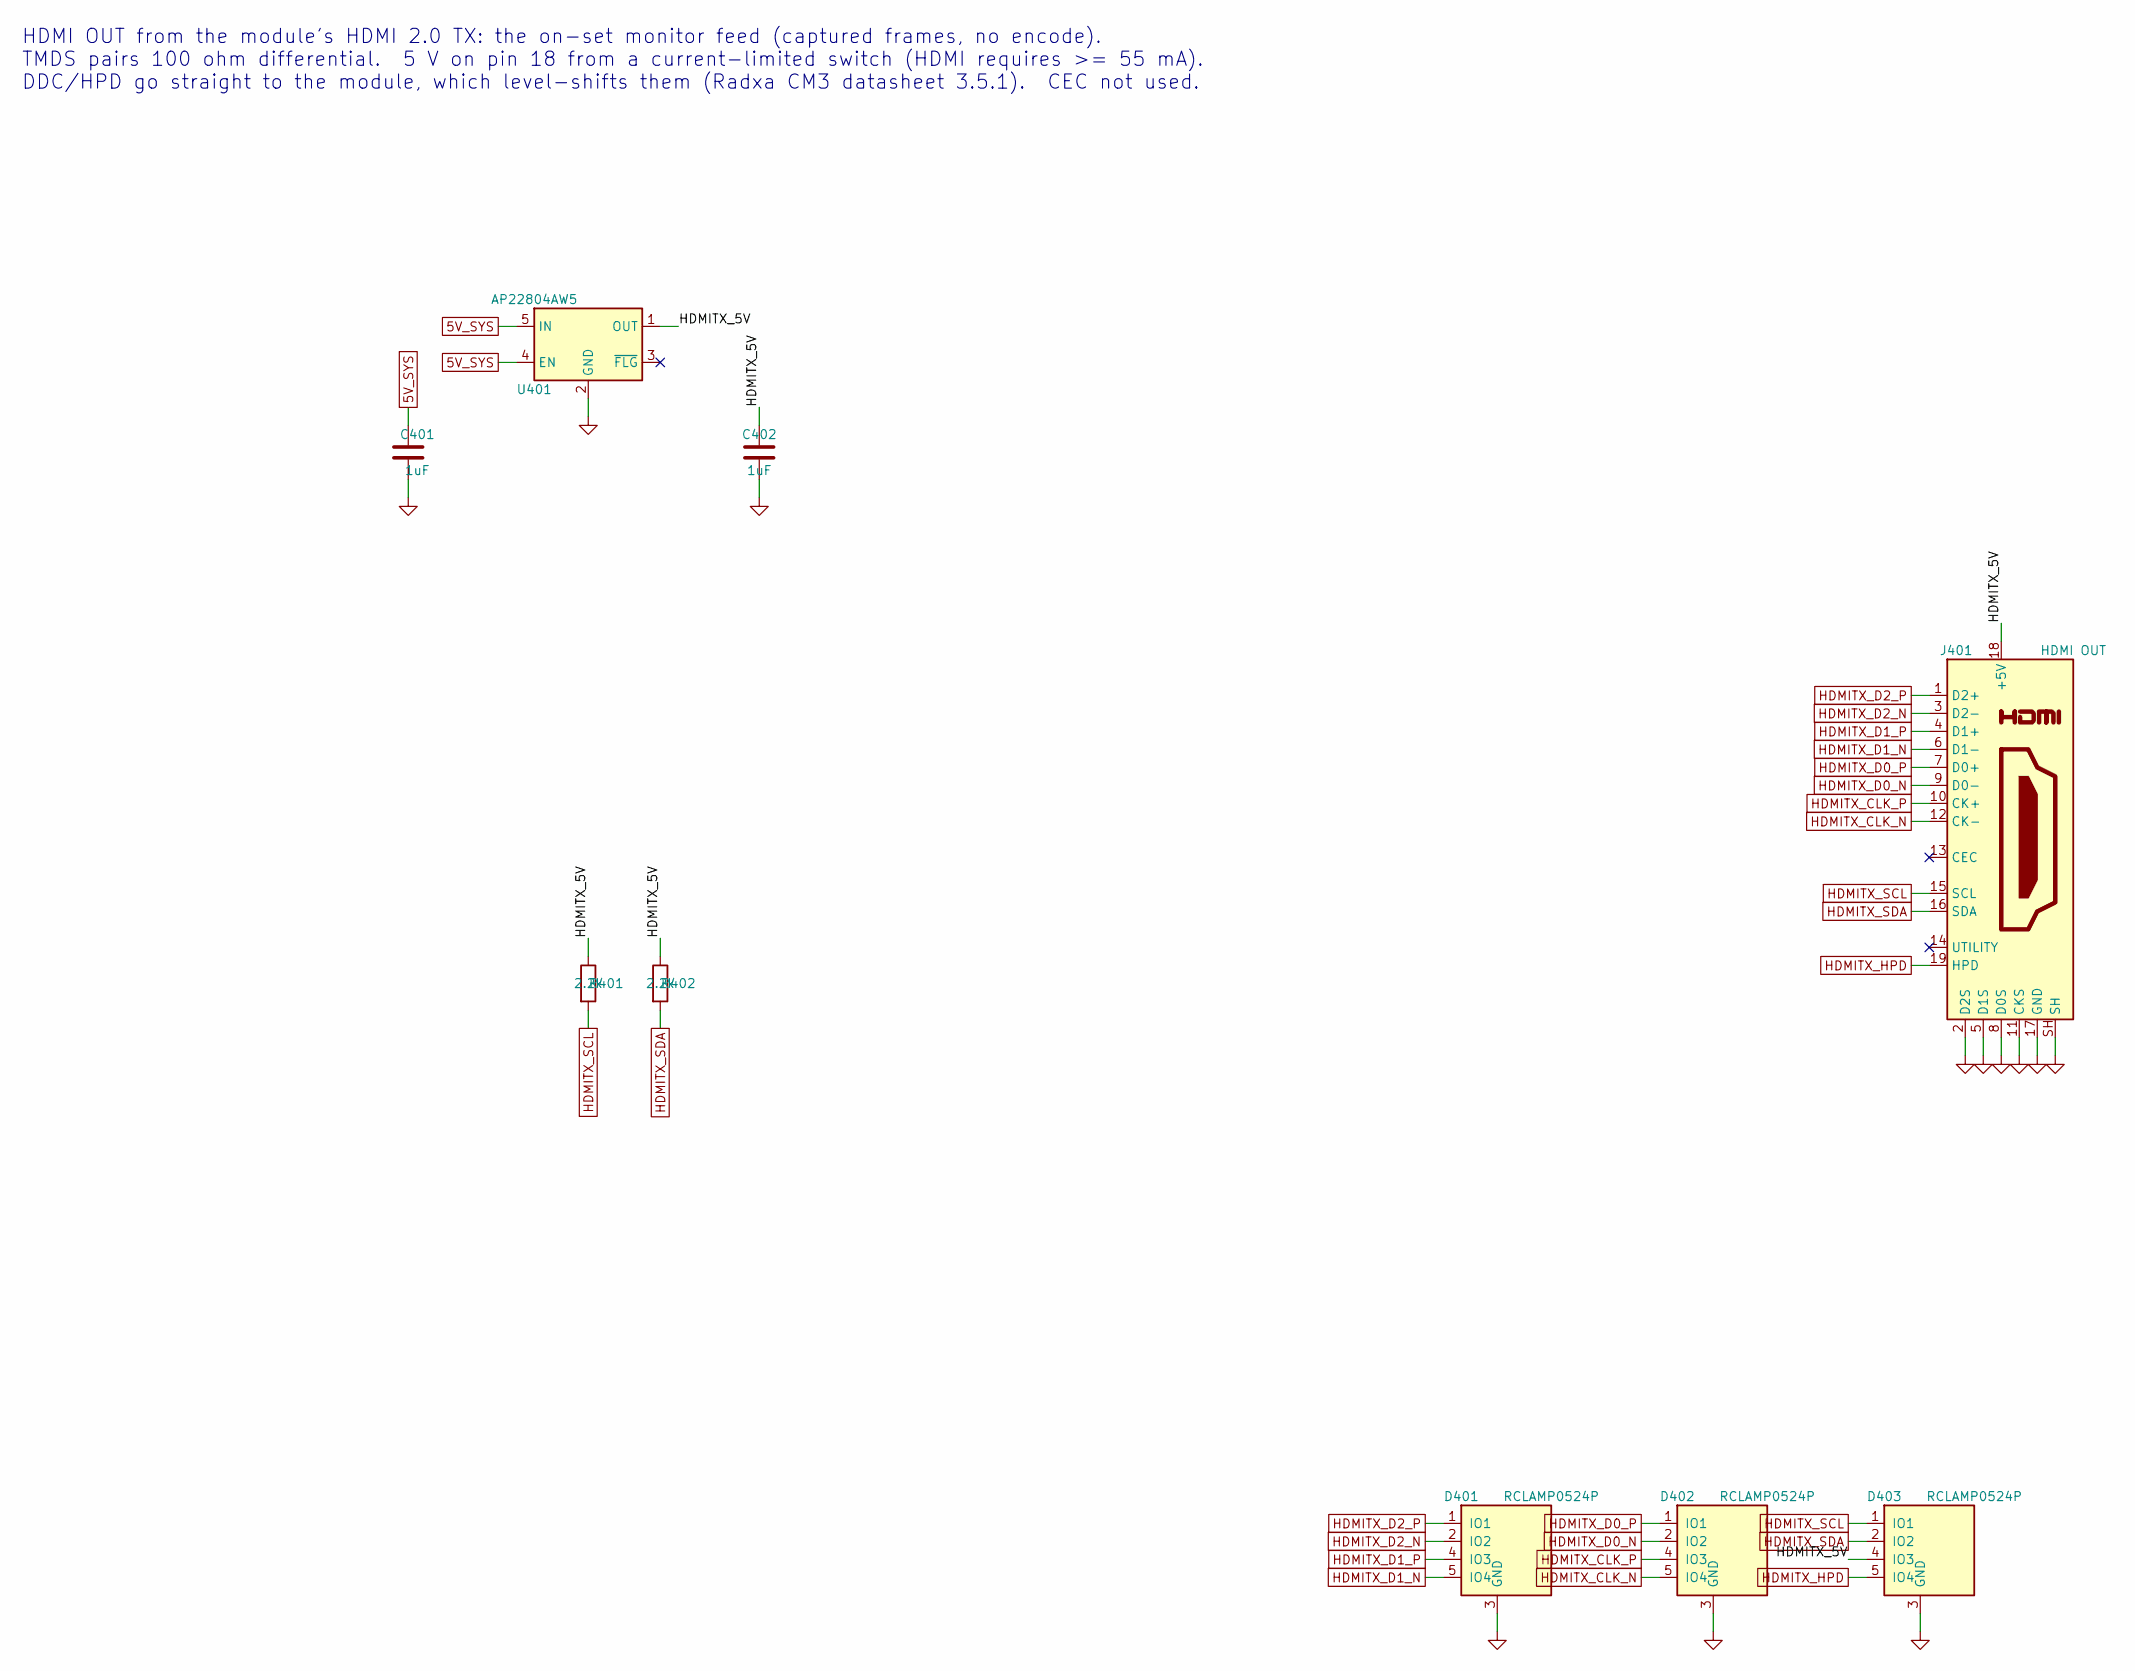
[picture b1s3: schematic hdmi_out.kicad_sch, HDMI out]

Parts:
C401, C402: 1uF; C_0402_1005Metric
D401, D402, D403: RCLAMP0524P; USON-10_2.5x1.0mm_P0.5mm; LCSC C907837
J401: HDMI OUT; HDMI_A_Molex_208658-1001_Horizontal
R401, R402: 2.2k; R_0402_1005Metric
U401: AP22804AW5; SOT-23-5

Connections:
5V_SYS: C401.1, U401.4 (EN), U401.5 (IN); also elsewhere on the board
/HDMI out/HDMITX_5V: C402.1, D403.4 (IO3), D403.7 (IO3), J401.18 (+5V), R401.1, R402.1, U401.1 (OUT)
GND: C401.2, C402.2, D401.3 (GND), D401.8 (GND), D402.3 (GND), D402.8 (GND), D403.3 (GND), D403.8 (GND), J401.2 (D2S), J401.5 (D1S), J401.8 (D0S), J401.11 (CKS), J401.17 (GND), J401.SH, U401.2 (GND); also elsewhere on the board
HDMITX_CLK_N: D402.5 (IO4), D402.6 (IO4), J401.12 (CK-); also elsewhere on the board
HDMITX_CLK_P: D402.4 (IO3), D402.7 (IO3), J401.10 (CK+); also elsewhere on the board
HDMITX_D0_N: D402.2 (IO2), D402.9 (IO2), J401.9 (D0-); also elsewhere on the board
HDMITX_D0_P: D402.1 (IO1), D402.10 (IO1), J401.7 (D0+); also elsewhere on the board
HDMITX_D1_N: D401.5 (IO4), D401.6 (IO4), J401.6 (D1-); also elsewhere on the board
HDMITX_D1_P: D401.4 (IO3), D401.7 (IO3), J401.4 (D1+); also elsewhere on the board
HDMITX_D2_N: D401.2 (IO2), D401.9 (IO2), J401.3 (D2-); also elsewhere on the board
HDMITX_D2_P: D401.1 (IO1), D401.10 (IO1), J401.1 (D2+); also elsewhere on the board
HDMITX_HPD: D403.5 (IO4), D403.6 (IO4), J401.19 (HPD); also elsewhere on the board
HDMITX_SCL: D403.1 (IO1), D403.10 (IO1), J401.15 (SCL), R401.2; also elsewhere on the board
HDMITX_SDA: D403.2 (IO2), D403.9 (IO2), J401.16 (SDA), R402.2; also elsewhere on the board

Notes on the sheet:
HDMI OUT from the module's HDMI 2.0 TX: the on-set monitor feed (captured frames, no encode). TMDS pairs 100 ohm differential. 5 V on pin 18 from a current-limited switch (HDMI requires >= 55 mA). DDC/HPD go straight to the module, which level-shifts them (Radxa CM3 datasheet 3.5.1). CEC not used.
